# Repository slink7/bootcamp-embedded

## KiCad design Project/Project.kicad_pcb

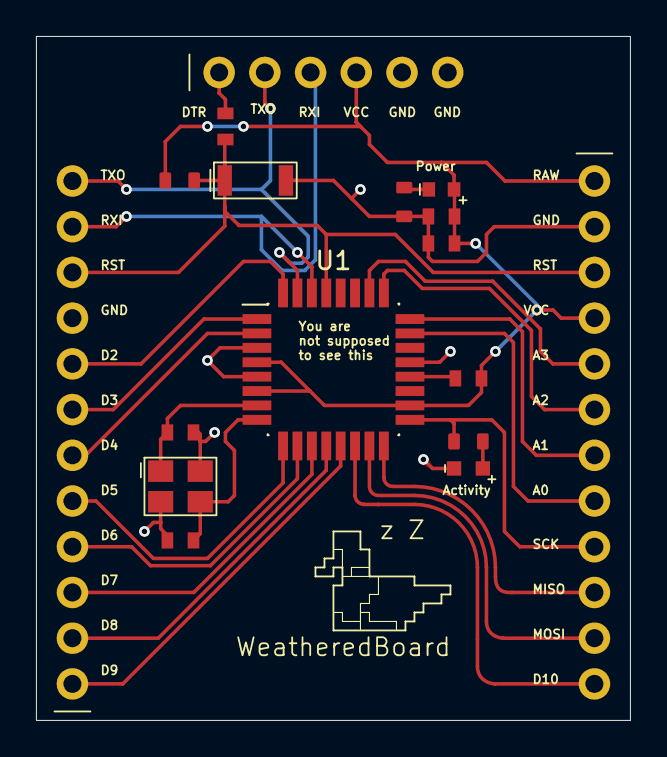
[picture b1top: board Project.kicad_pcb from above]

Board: 2 copper layers, 33.0 x 38.0 mm, 17 parts (0 on the bottom side), 27 nets.

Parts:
C1, C2: 12pF; FCC0603
C3, C4, C7: 100nF; FCC0603
C6: 1uF; FCC0603
D1: Green; TZ-P2-0603YGTCS1-0.6T
D2: Red; XL-1608SURC-06 (RED)
J1, J2: 12Pins2.54
J3: 6Pins2.54
R1: 330; FRC0603
R2, R3: 10k; FRC0603
SW_Push1: B3U-1000P
U1: ATmega328P-A; QFP-32_7x7_Pitch0.8mm
Y1: 16MHz; Crystal

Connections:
A0: J2.8, U1.23 (PC0)
A1: J2.7, U1.24 (PC1)
A2: J2.6, U1.25 (PC2)
A3: J2.5, U1.26 (PC3)
D2: J1.8, U1.32 (PD2)
D3: J1.7, U1.1 (PD3)
D4: J1.6, U1.2 (PD4)
D5: J1.5, U1.9 (PD5)
D6: J1.4, U1.10 (PD6)
D7: J1.3, U1.11 (PD7)
D8: J1.2, U1.12 (PB0)
D9: J1.1, U1.13 (PB1)
D10: J2.12, U1.14 (PB2)
DTR: C4.1, J3.1
GND: C1.2, C2.2, C6.1, C7.1, D1.1, J1.9, J2.2, J3.5, J3.6, R2.2, SW_Push1.2, U1.3 (GND), U1.5, U1.21, Y1.2, Y1.4
MISO: J2.10, U1.16 (PB4)
MOSI: J2.11, U1.15 (PB3)
unnamed: D1.2, R1.1
unnamed: D2.1, R2.1
unnamed: C3.2, U1.20 (AREF)
unnamed: C2.1, U1.7 (XTAL1/PB6), Y1.1
unnamed: C1.1, U1.8 (XTAL2/PB7), Y1.3
RAW: C3.1, C6.2, C7.2, D2.2, J2.1, J2.4, J3.4, R3.1, U1.4 (VCC), U1.6, U1.18 (AVCC)
RST: C4.2, J1.10, J2.3, R3.2, SW_Push1.1, U1.29 (RESET/PC6)
RXI: J1.11, J3.3, U1.30 (PD0)
SCK: J2.9, R1.2, U1.17 (PB5)
TXO: J1.12, J3.2, U1.31 (PD1)
